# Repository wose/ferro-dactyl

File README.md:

# Ferro Dactyl

> A BluePill (STM32F103) based [Dactyl-Manuform] build with [keyberon] powered
> firmware written in Rust. 

[Dactyl-Manuform]: https://github.com/20lives/Dactyl-Manuform
[keyberon]: https://github.com/TeXitoi/keyberon

## Layout

I'm using a [AdNW] based Layout. This is a work in progress.

You can take the layout definition from the [layout folder] and play with it
over at [Keyboard Layout Editor]. Or use [this link].

[AdNW]: http://www.adnw.de/
[layout folder]:layout/
[Keyboard Layout Editor]: http://www.keyboard-layout-editor.com/
[this link]: http://www.keyboard-layout-editor.com/#/gists/5a7d56aa6b7ebb05c0e3928ac5250a80

## Hardware

The [STLs] are generated using [20lives Dactyl-Manuform fork]. I'm using a 5x6
version.

[STLs]: stl/
[20lives Dactyl-Manuform fork]:  https://github.com/20lives/Dactyl-Manuform

## Firmware

The firmware uses the [keyberon] library.

```shell
curl https://sh.rustup.rs -sSf | sh
rustup target add thumbv7m-none-eabi
sudo apt-get install gdb-arm-none-eabi openocd
git clone https://github.com/wose/ferro-dactyl.git
cd ferro-dactyl
# connect ST-Link v2 to the blue pill and the computer
# openocd in another terminal
cargo run --release
```
See `keyberons` [building instructions] for more info.

[building instructions]: https://github.com/TeXitoi/keyberon/blob/master/BUILDING.md

## License

Licensed under either of

- Apache License, Version 2.0 ([LICENSE-APACHE](LICENSE-APACHE) or
  http://www.apache.org/licenses/LICENSE-2.0)
- MIT license ([LICENSE-MIT](LICENSE-MIT) or http://opensource.org/licenses/MIT)

at your option.

### Contribution

Unless you explicitly state otherwise, any contribution intentionally submitted
for inclusion in the work by you, as defined in the Apache-2.0 license, shall be
dual licensed as above, without any additional terms or conditions.

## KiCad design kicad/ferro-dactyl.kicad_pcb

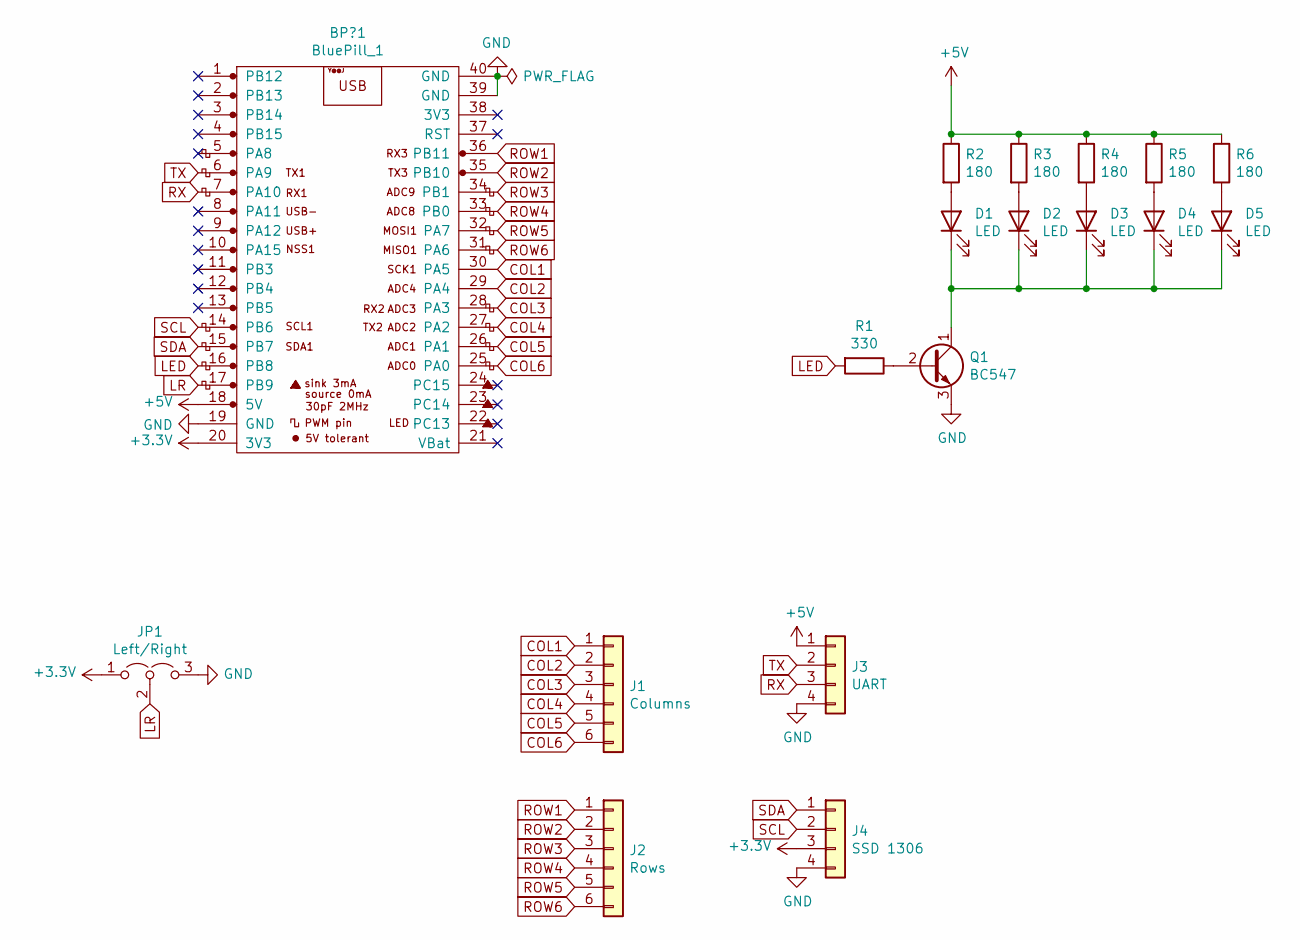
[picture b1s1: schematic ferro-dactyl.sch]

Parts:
BP?1: BluePill_1; YAAJ_BluePill_SWD_1
D1, D2, D3, D4, D5: LED; PinSocket_1x02_P2.54mm_Vertical
J1: Columns; PinSocket_1x06_P2.54mm_Vertical
J2: Rows; PinSocket_1x06_P2.54mm_Vertical
J3: UART; PinSocket_1x04_P2.54mm_Vertical
J4: SSD 1306; PinSocket_1x04_P2.54mm_Vertical
JP1: Left/Right; PinHeader_1x03_P2.54mm_Vertical
Q1: BC547; TO-92_Inline
R1: 330; R_Axial_DIN0411_L9.9mm_D3.6mm_P12.70mm_Horizontal
R2, R3, R4, R5, R6: 180; R_Axial_DIN0411_L9.9mm_D3.6mm_P12.70mm_Horizontal

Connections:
+3V3: BP?1.20 (3V3), J4.3, JP1.1 (A)
+5V: BP?1.18 (5V), J3.1, R2.1, R3.1, R4.1, R5.1, R6.1
COL1: BP?1.30 (PA5), J1.1
COL2: BP?1.29 (PA4), J1.2
COL3: BP?1.28 (PA3), J1.3
COL4: BP?1.27 (PA2), J1.4
COL5: BP?1.26 (PA1), J1.5
COL6: BP?1.25 (PA0), J1.6
GND: BP?1.19 (GND), BP?1.39 (GND), BP?1.40 (GND), J3.4, J4.4, JP1.3 (B), Q1.3 (E)
LED: BP?1.16 (PB8), R1.2
LR: BP?1.17 (PB9), JP1.2 (C)
unnamed: D1.1 (K), D2.1 (K), D3.1 (K), D4.1 (K), D5.1 (K), Q1.1 (C)
unnamed: D1.2 (A), R2.2
unnamed: D2.2 (A), R3.2
unnamed: D3.2 (A), R4.2
unnamed: D4.2 (A), R5.2
unnamed: D5.2 (A), R6.2
unnamed: Q1.2 (B), R1.1
ROW1: BP?1.36 (PB11), J2.1
ROW2: BP?1.35 (PB10), J2.2
ROW3: BP?1.34 (PB1), J2.3
ROW4: BP?1.33 (PB0), J2.4
ROW5: BP?1.32 (PA7), J2.5
ROW6: BP?1.31 (PA6), J2.6
RX: BP?1.7 (PA10), J3.3
SCL: BP?1.14 (PB6), J4.2
SDA: BP?1.15 (PB7), J4.1
TX: BP?1.6 (PA9), J3.2

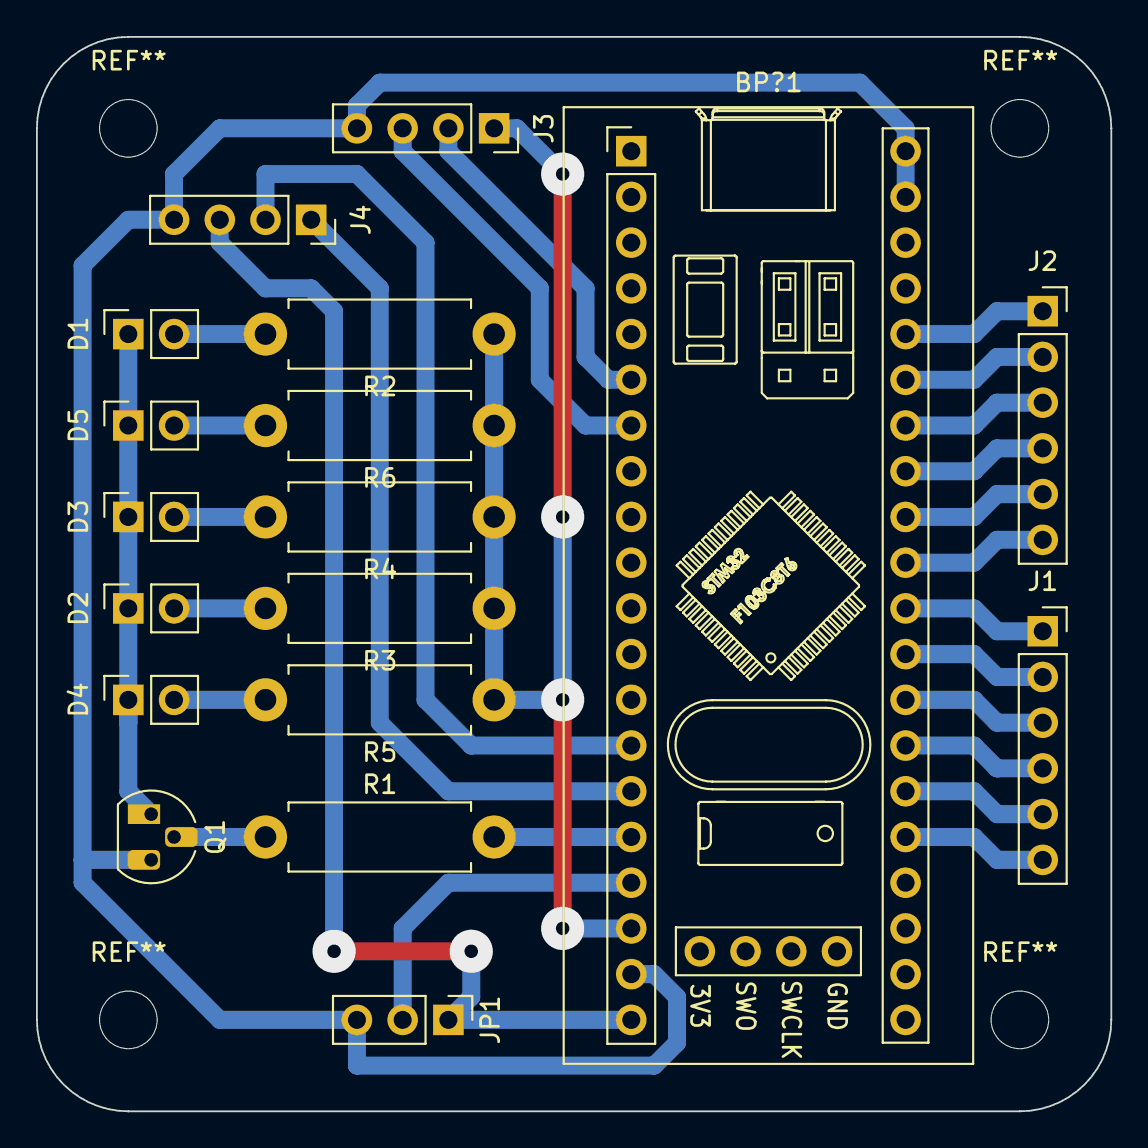
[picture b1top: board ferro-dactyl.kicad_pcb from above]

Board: 2 copper layers, 59.7 x 59.7 mm, 18 parts (0 on the bottom side), 28 nets.

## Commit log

2020-07-06 Init
2020-07-06 Adds STLs, layout and some images
2020-07-06 Fixes build instructions
2020-07-06 Fixes Dactyl-Manuform link
2020-07-06 Adds logo
2020-07-07 Adds KiCAD project
2020-07-11 Changes RJ9 connector to 3.5mm jack
2020-07-17 Reduces wall thickness for jack mount
2020-11-09 Adds pcb
2020-11-09 Adds base plate FreeCAD project for CNC milling
2022-06-16 rewrite for stm32f411
